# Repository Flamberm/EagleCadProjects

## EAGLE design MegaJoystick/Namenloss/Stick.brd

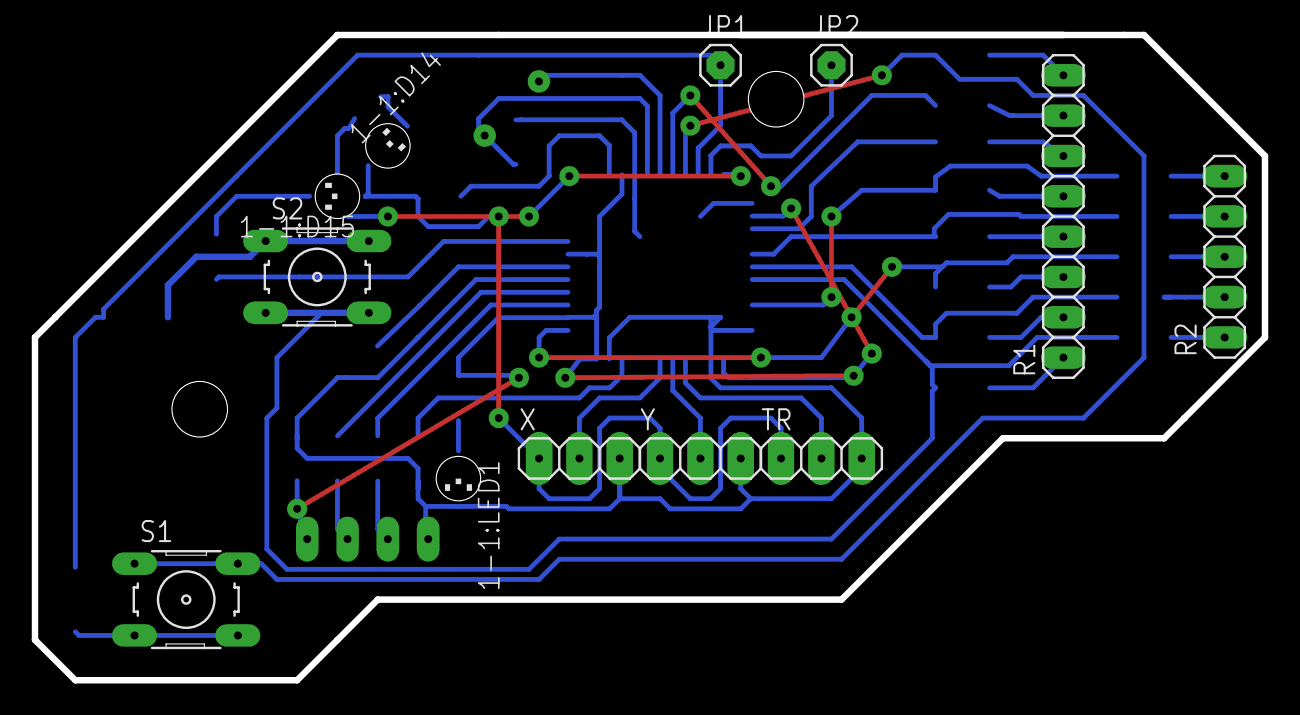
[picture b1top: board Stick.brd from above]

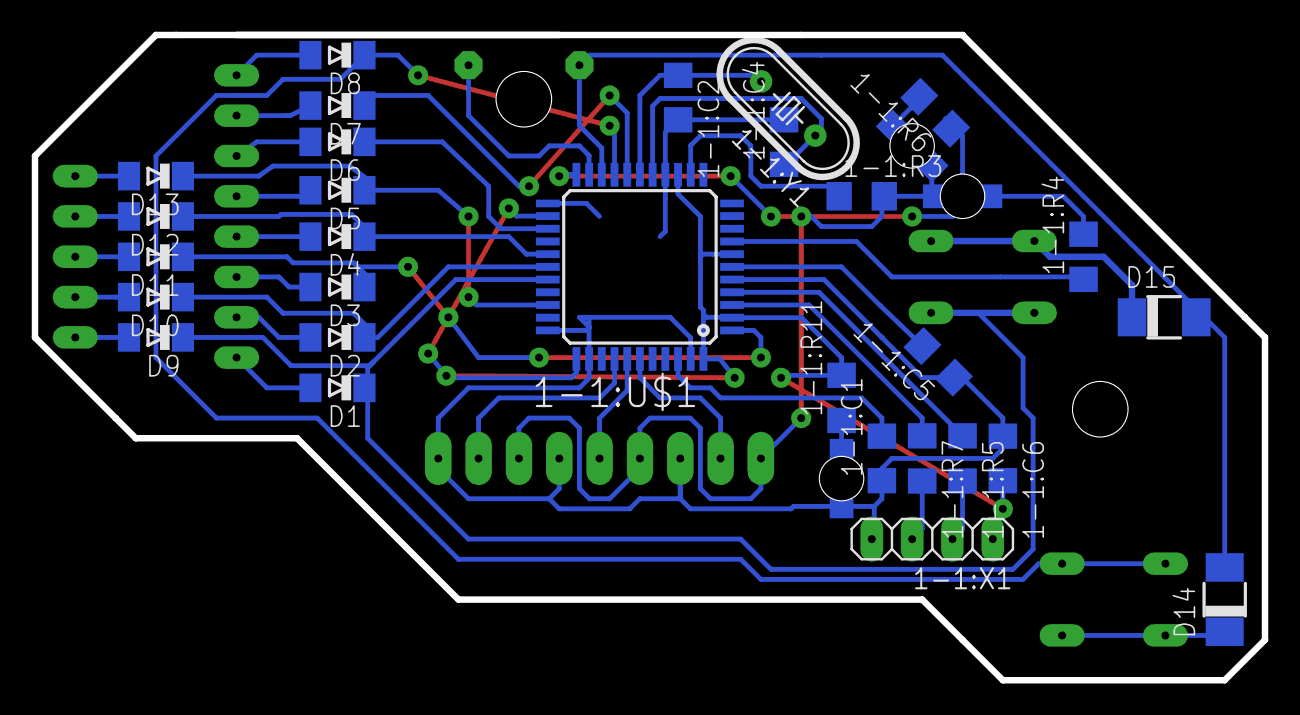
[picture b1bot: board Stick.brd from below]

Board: 2 copper layers, 77.5 x 40.6 mm, 42 parts (29 on the bottom side), 45 nets.

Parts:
1-1:C1, 1-1:C5, 1-1:C6: 10uF; C1206
1-1:C2, 1-1:C4: 22pF; C1206
1-1:D14: GREEN; LED1206
1-1:D15: RED; LED1206
1-1:FRAME1: FRAME-LETTER; CREATIVE_COMMONS
1-1:LED1: BLUE; LED1206
1-1:R3: 10K; R1206
1-1:R4: 300R; R1206
1-1:R5, 1-1:R7: 27R; R1206
1-1:R6, 1-1:R11: 390R; R1206
1-1:U$1: ATMEGA32U4-AU; TQFP44
1-1:X1: 1X04
1-1:Y1: 16MHz; HC49/S
D1, D2, D3, D4, D5, D6, D7, D8, D9, D10, D11, D12, D13: MINIMELF
D14, D15: DO-214AC
JP1, JP2: 1X01
R1: 1X08
R2: 1X05
S1, S2: B3F-10XX
TR: 1X03
X: 1X03
Y: 1X03

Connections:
1-1:3.3V: 1-1:C6.2, 1-1:R11.2, 1-1:U$1.2, 1-1:U$1.7, 1-1:U$1.14, 1-1:U$1.24, 1-1:U$1.34, 1-1:U$1.44, 1-1:X1.1
1-1:AREF: 1-1:C1.2, 1-1:U$1.42
1-1:D14: 1-1:R4.1, 1-1:U$1.8
1-1:D+: 1-1:R5.1, 1-1:U$1.4
1-1:D-: 1-1:R7.1, 1-1:U$1.3
1-1:N$23: 1-1:C4.1, 1-1:U$1.16, 1-1:Y1.1
1-1:N$24: 1-1:C2.1, 1-1:U$1.17, 1-1:Y1.2
1-1:N$25: 1-1:C5.2, 1-1:U$1.6
1-1:N$26: 1-1:R7.2, 1-1:X1.3
1-1:N$27: 1-1:R5.2, 1-1:X1.2
1-1:N$29: 1-1:D15.C, 1-1:R4.2
1-1:N$30: 1-1:D14.C, 1-1:R6.2
1-1:N$38: 1-1:LED1.A, 1-1:R11.1
1-1:RESET: 1-1:R3.1, 1-1:U$1.13
1-1:TXLED: 1-1:R6.1, 1-1:U$1.22
D2: 1-1:U$1.19, D8.C, S1.1, S1.2
D9: 1-1:U$1.29, D1.C, D9.C, S2.3, S2.4
GND: 1-1:C1.1, 1-1:C2.2, 1-1:C4.2, 1-1:C5.1, 1-1:C6.1, 1-1:LED1.C, 1-1:U$1.5, 1-1:U$1.15, 1-1:U$1.23, 1-1:U$1.33, 1-1:U$1.35, 1-1:U$1.43, 1-1:X1.4, TR.3, X.3, Y.3
unnamed: D15.C, S2.1, S2.2
unnamed: 1-1:U$1.21, JP2.1
unnamed: D1.A, R1.1
unnamed: D2.A, R1.2
unnamed: D3.A, R1.3
unnamed: D4.A, R1.4
unnamed: D5.A, R1.5
unnamed: D6.A, R1.6
unnamed: D7.A, R1.7
unnamed: D8.A, R1.8
unnamed: D9.A, R2.1
unnamed: D10.A, R2.2
unnamed: D11.A, R2.3
unnamed: D12.A, R2.4
unnamed: D13.A, R2.5
unnamed: 1-1:D14.A, 1-1:D15.A, 1-1:R3.2, TR.1, X.1, Y.1
unnamed: 1-1:U$1.39, X.2
unnamed: 1-1:U$1.38, Y.2
unnamed: 1-1:U$1.37, TR.2
unnamed: D14.C, S1.3, S1.4
R2: 1-1:U$1.28, D2.C, D10.C
R3: 1-1:U$1.1, D3.C, D11.C
R4: 1-1:U$1.27, D4.C, D12.C
R5: 1-1:U$1.31, D5.C, D13.C
R6: 1-1:U$1.25, D6.C
R7: 1-1:U$1.18, D7.C
RXI: 1-1:U$1.20, D14.A, D15.A, JP1.1

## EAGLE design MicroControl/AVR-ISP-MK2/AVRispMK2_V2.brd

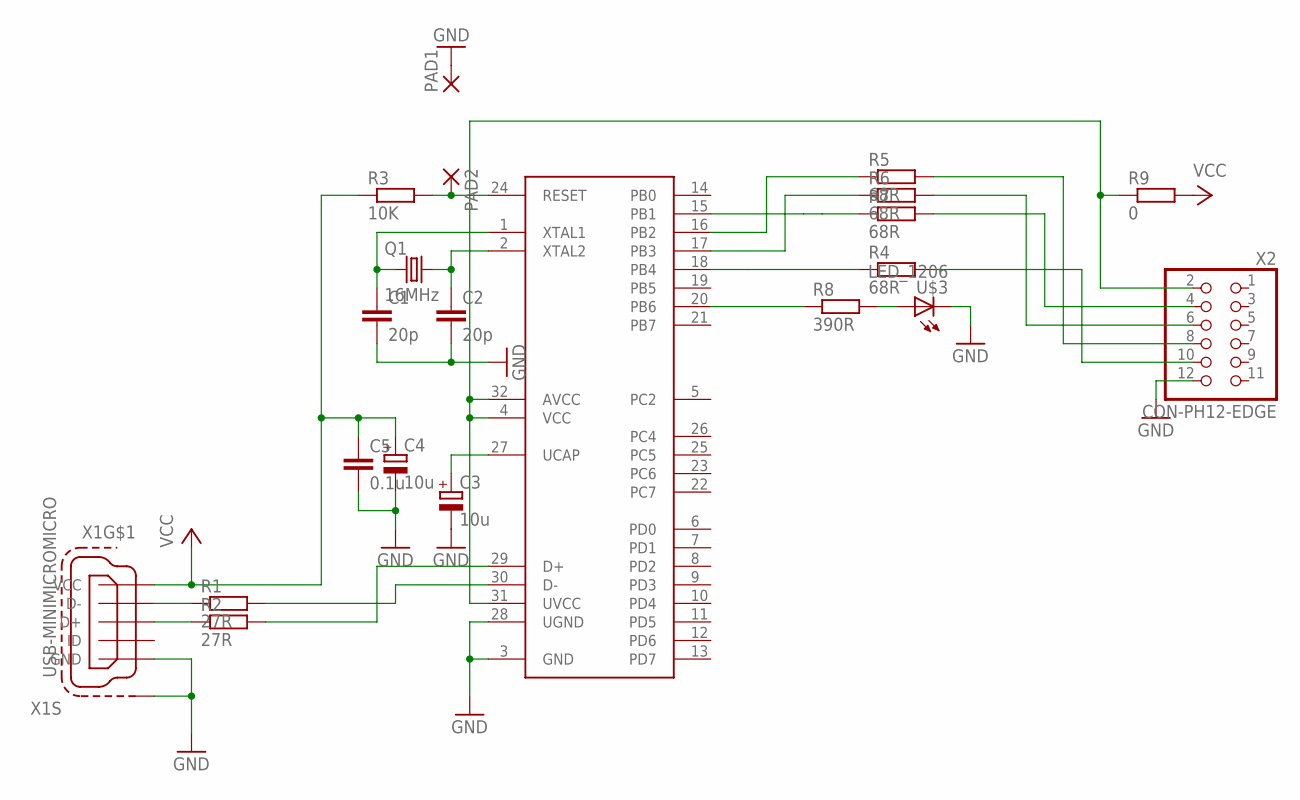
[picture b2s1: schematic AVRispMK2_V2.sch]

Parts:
C1, C2: 20p; C1206
C3, C4: 10u; SMC_A
C5: 0.1u; C1206
PAD1, PAD2: SMD2; SMD1,27-2,54
Q1: 16MHz; CRYSTAL-3225
R1, R2: 27R; R1206
R3: 10K; R1206
R4, R5, R6, R7: 68R; R1206
R8: 390R; R1206
R9: 0; R1206
U$1: AT90USB162; VQFP32
U$3: LED_1206; LED1206
X1: USB-MINIMICROMICRO; USB-B-MICRO-SMD
X2: CON-PH12-EDGE; ML12_EDGE_SMD

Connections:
!RST: R4.2, X2.10
GND: C1.2, C2.2, C3.-, C4.-, C5.2, PAD1.1, U$1.3 (GND), U$1.28 (UGND), U$3.C, X1.GND, X1.SHIELD1 (S1), X1.SHIELD2 (S1), X1.SHIELD3 (S1), X2.12
MISO: R6.2, X2.6
MOSI: R5.2, X2.8
unnamed: R2.1, X1.D+
unnamed: R1.1, X1.D-
unnamed: C1.1, Q1.P$2 (1), U$1.1 (XTAL1)
unnamed: C2.1, Q1.P$4 (2), U$1.2 (XTAL2)
unnamed: R1.2, U$1.30 (D-)
unnamed: R2.2, U$1.29 (D+)
unnamed: C3.+, U$1.27 (UCAP)
unnamed: PAD2.1, R3.2, U$1.24 (RESET)
unnamed: R8.1, U$1.20 (PB6)
unnamed: R8.2, U$3.A
unnamed: R4.1, U$1.18 (PB4)
unnamed: R6.1, U$1.17 (PB3)
unnamed: R5.1, U$1.16 (PB2)
unnamed: R7.1, U$1.15 (PB1)
SCK: R7.2, X2.4
VCC: C4.+, C5.1, R3.1, R9.2, X1.VBUS (VCC)
VTRG: R9.1, U$1.4 (VCC), U$1.31 (UVCC), U$1.32 (AVCC), X2.2

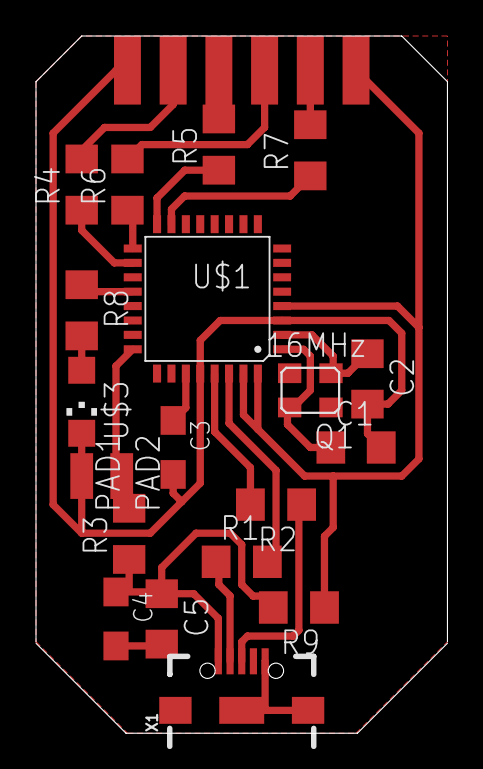
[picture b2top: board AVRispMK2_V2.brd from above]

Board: 2 copper layers, 22.9 x 38.7 mm, 21 parts (1 on the bottom side), 21 nets.

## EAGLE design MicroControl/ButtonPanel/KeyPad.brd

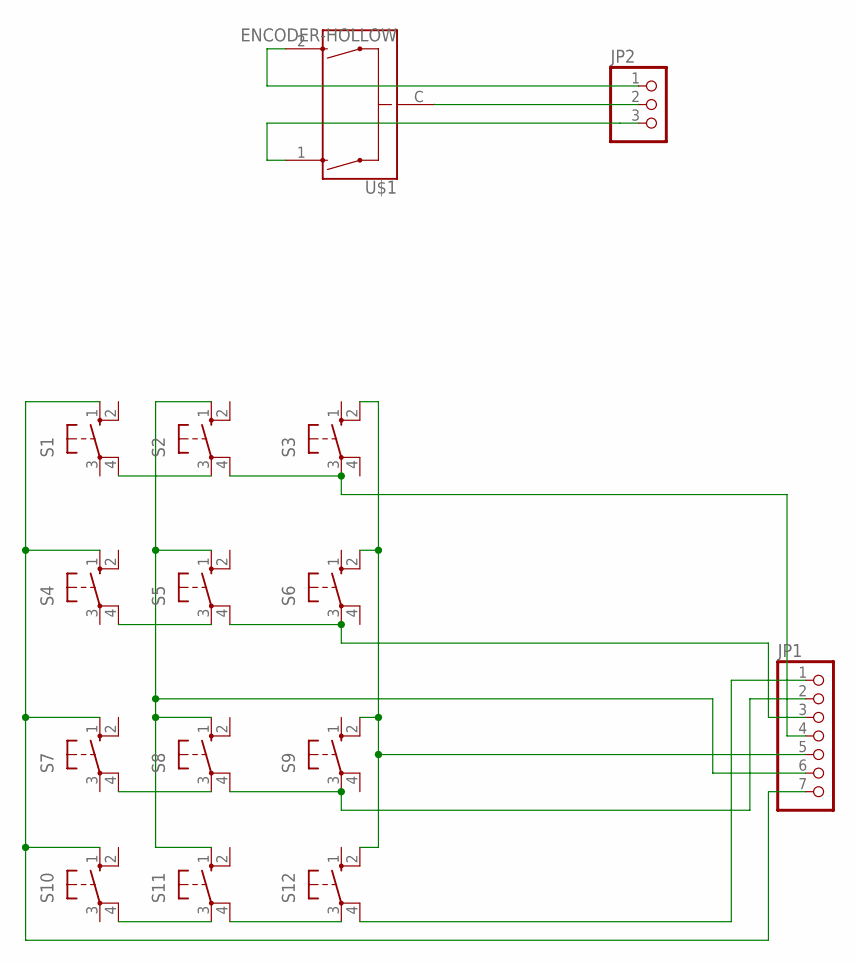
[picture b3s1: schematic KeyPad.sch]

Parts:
JP1: PINHD-1X7/90; 1X07/90
JP2: PINHD-1X3/90; 1X03/90
S1, S2, S3, S4, S5, S6, S7, S8, S9, S10, S11, S12: 40-XX; B3F-40XX
U$1: ENCODER-HOLLOW; HOLLOW-ENCODER

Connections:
unnamed: JP2.2, U$1.C
unnamed: JP2.1, U$1.2 (B)
unnamed: JP2.3, U$1.1 (A)
unnamed: S10.4 (P1), S11.3
unnamed: S11.4 (P1), S12.3
unnamed: JP1.2, S8.4 (P1), S9.3
unnamed: S7.4 (P1), S8.3
unnamed: S4.4 (P1), S5.3
unnamed: JP1.3, S5.4 (P1), S6.3
unnamed: S1.4 (P1), S2.3
unnamed: JP1.4, S2.4 (P1), S3.3
unnamed: JP1.1, S12.4 (P1)
unnamed: JP1.7, S1.1 (S), S4.1 (S), S7.1 (S), S10.1 (S)
unnamed: JP1.6, S2.1 (S), S5.1 (S), S8.1 (S), S11.1 (S)
unnamed: JP1.5, S3.2 (S1), S6.2 (S1), S9.2 (S1), S12.2 (S1)

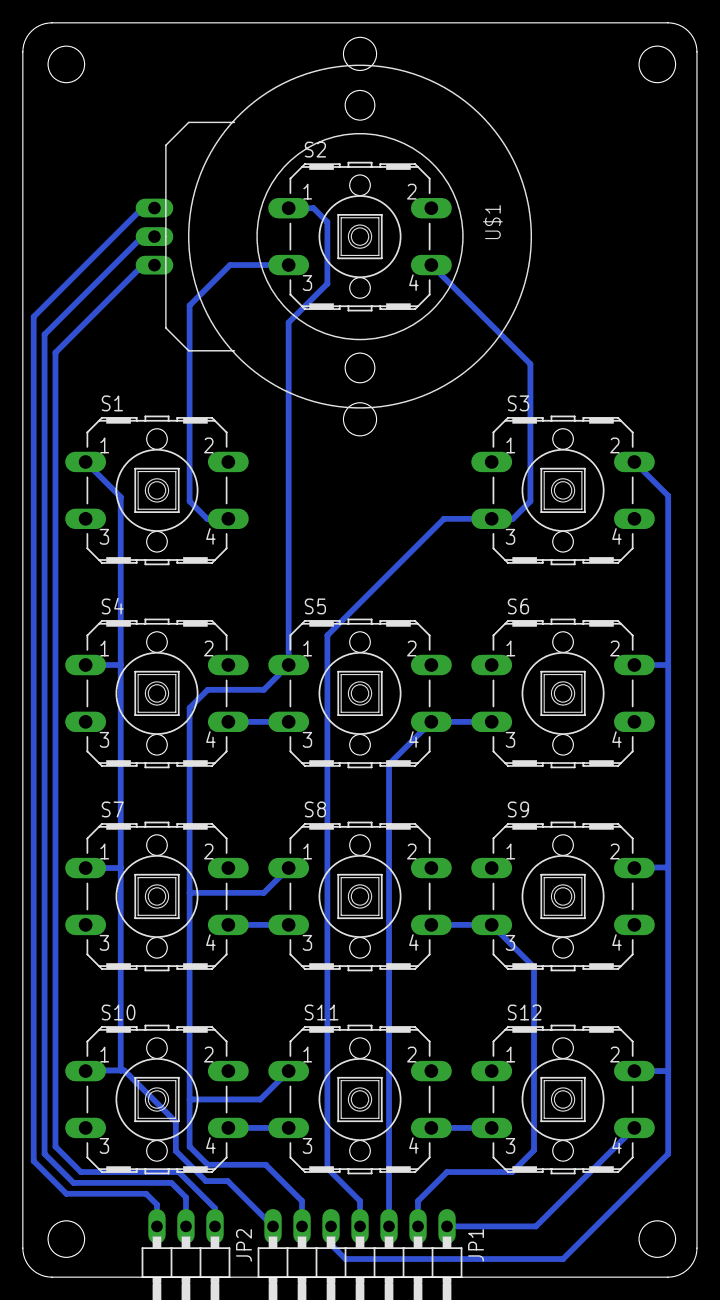
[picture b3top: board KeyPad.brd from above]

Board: 2 copper layers, 59.0 x 109.8 mm, 15 parts (0 on the bottom side), 15 nets.

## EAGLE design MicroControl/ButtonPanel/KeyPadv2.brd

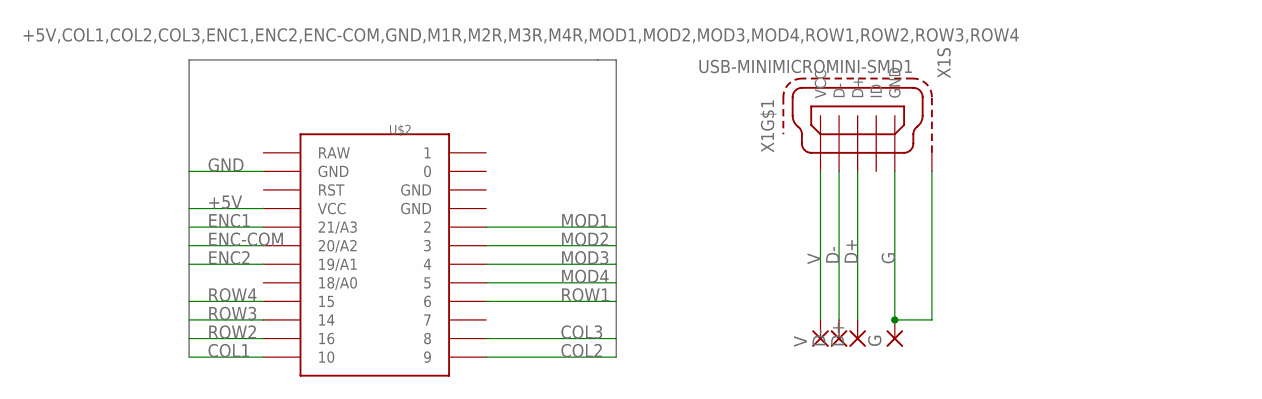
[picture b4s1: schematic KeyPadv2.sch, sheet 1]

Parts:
D+: SMD2; SMD1,27-2,54
D-: SMD2; SMD1,27-2,54
G: SMD2; SMD1,27-2,54
U$2: PROMICRO
V: SMD2; SMD1,27-2,54
X1: USB-MINIMICROMINI-SMD1; 32005-201

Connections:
0: U$2.0
1: U$2.1
+5V: U$2.VCC
COL1: U$2.10; also elsewhere on the board
COL2: U$2.9; also elsewhere on the board
COL3: U$2.8; also elsewhere on the board
D+: D+.1, X1.3 (D+)
D-: D-.1, X1.2 (D-)
ENC1: U$2.21/A3; also elsewhere on the board
ENC2: U$2.19/A1; also elsewhere on the board
ENC-COM: U$2.20/A2; also elsewhere on the board
G: G.1, X1.5 (GND), X1.M1 (S1), X1.M2 (S1), X1.M3 (S1), X1.M4 (S1)
GND: U$2.GND@1 (GND), U$2.GND@2 (GND); also elsewhere on the board
MOD1: U$2.2; also elsewhere on the board
MOD2: U$2.3; also elsewhere on the board
MOD3: U$2.4; also elsewhere on the board
MOD4: U$2.5; also elsewhere on the board
RAW: U$2.RAW
ROW1: U$2.6; also elsewhere on the board
ROW2: U$2.16; also elsewhere on the board
ROW3: U$2.14; also elsewhere on the board
ROW4: U$2.15; also elsewhere on the board
V: V.1, X1.1 (VCC)

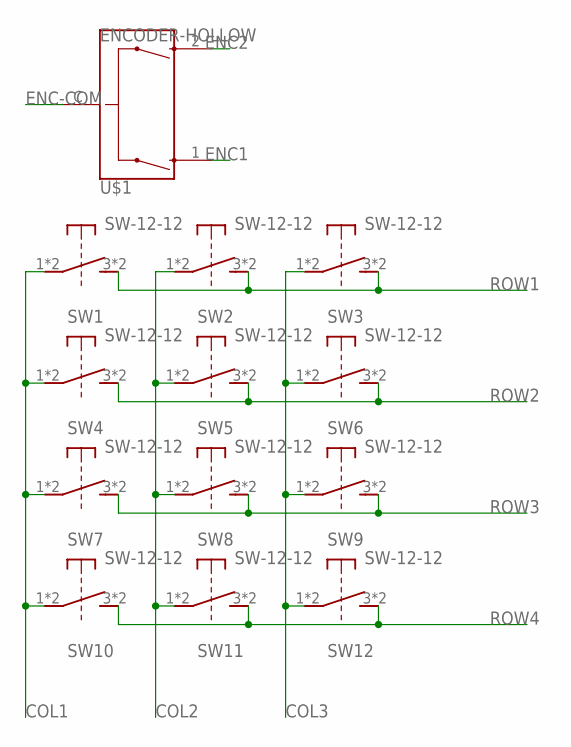
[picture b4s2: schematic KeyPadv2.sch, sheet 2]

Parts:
SW1, SW2, SW3, SW4, SW5, SW6, SW7, SW8, SW9, SW10, SW11, SW12: SW-12-12; B3F-40XX
U$1: ENCODER-HOLLOW; HOLLOW-ENCODER

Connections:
COL1: SW1.1, SW1.2 (1), SW4.1, SW4.2 (1), SW7.1, SW7.2 (1), SW10.1, SW10.2 (1); also elsewhere on the board
COL2: SW2.1, SW2.2 (1), SW5.1, SW5.2 (1), SW8.1, SW8.2 (1), SW11.1, SW11.2 (1); also elsewhere on the board
COL3: SW3.1, SW3.2 (1), SW6.1, SW6.2 (1), SW9.1, SW9.2 (1), SW12.1, SW12.2 (1); also elsewhere on the board
ENC1: U$1.1 (A); also elsewhere on the board
ENC2: U$1.2 (B); also elsewhere on the board
ENC-COM: U$1.C; also elsewhere on the board
ROW1: SW1.3 (2), SW1.4 (2), SW2.3 (2), SW2.4 (2), SW3.3 (2), SW3.4 (2); also elsewhere on the board
ROW2: SW4.3 (2), SW4.4 (2), SW5.3 (2), SW5.4 (2), SW6.3 (2), SW6.4 (2); also elsewhere on the board
ROW3: SW7.3 (2), SW7.4 (2), SW8.3 (2), SW8.4 (2), SW9.3 (2), SW9.4 (2); also elsewhere on the board
ROW4: SW10.3 (2), SW10.4 (2), SW11.3 (2), SW11.4 (2), SW12.3 (2), SW12.4 (2); also elsewhere on the board

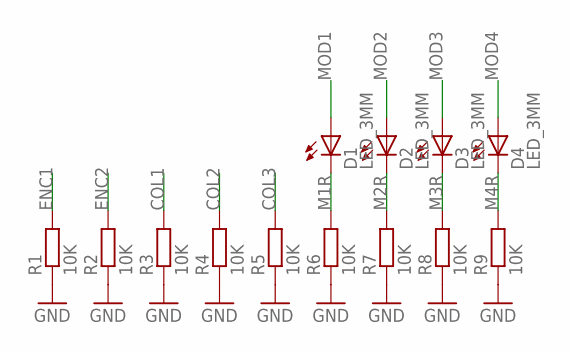
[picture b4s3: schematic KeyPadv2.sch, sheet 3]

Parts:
D1, D2, D3, D4: LED_3MM; LED3MM
R1, R2, R3, R4, R5, R6, R7, R8, R9: 10K; RESC3216X60

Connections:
COL1: R3.2; also elsewhere on the board
COL2: R4.2; also elsewhere on the board
COL3: R5.2; also elsewhere on the board
ENC1: R1.2; also elsewhere on the board
ENC2: R2.2; also elsewhere on the board
GND: R1.1, R2.1, R3.1, R4.1, R5.1, R6.1, R7.1, R8.1, R9.1; also elsewhere on the board
M1R: D1.K (C), R6.2
M2R: D2.K (C), R7.2
M3R: D3.K (C), R8.2
M4R: D4.K (C), R9.2
MOD1: D1.A; also elsewhere on the board
MOD2: D2.A; also elsewhere on the board
MOD3: D3.A; also elsewhere on the board
MOD4: D4.A; also elsewhere on the board

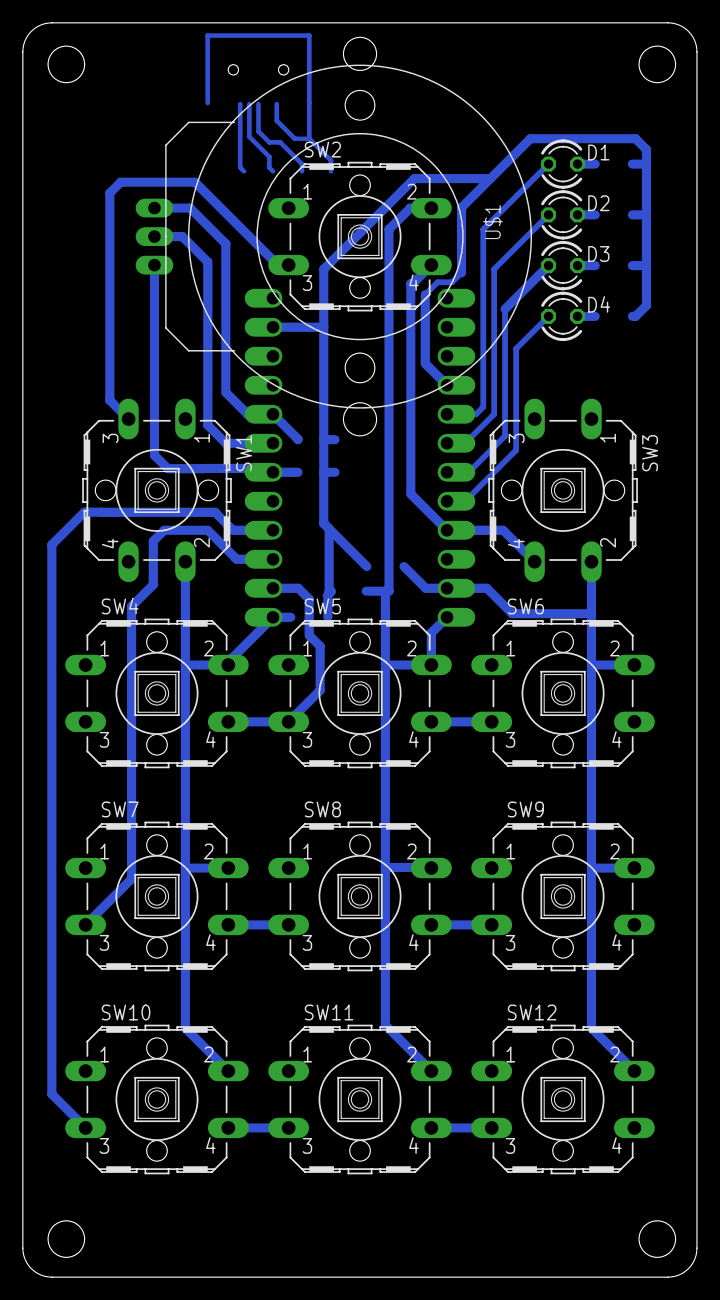
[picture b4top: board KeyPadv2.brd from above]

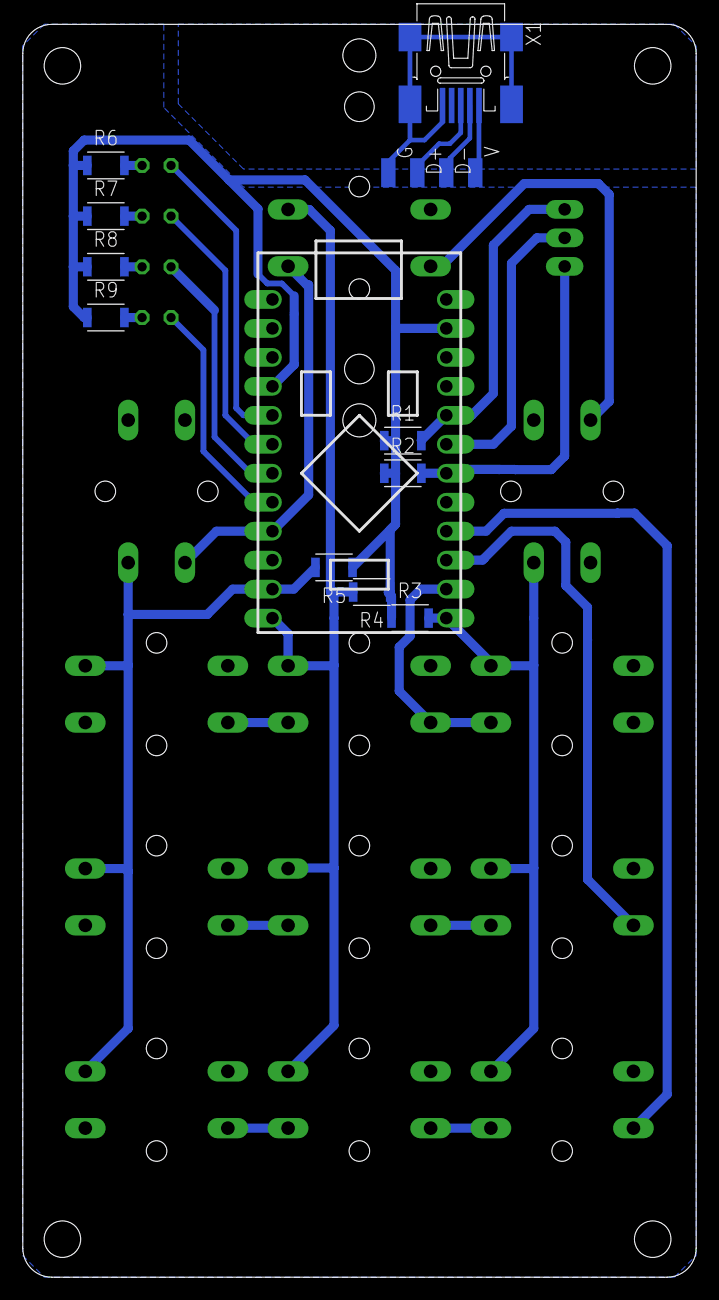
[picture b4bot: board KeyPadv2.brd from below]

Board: 2 copper layers, 59.0 x 109.8 mm, 32 parts (15 on the bottom side), 23 nets.

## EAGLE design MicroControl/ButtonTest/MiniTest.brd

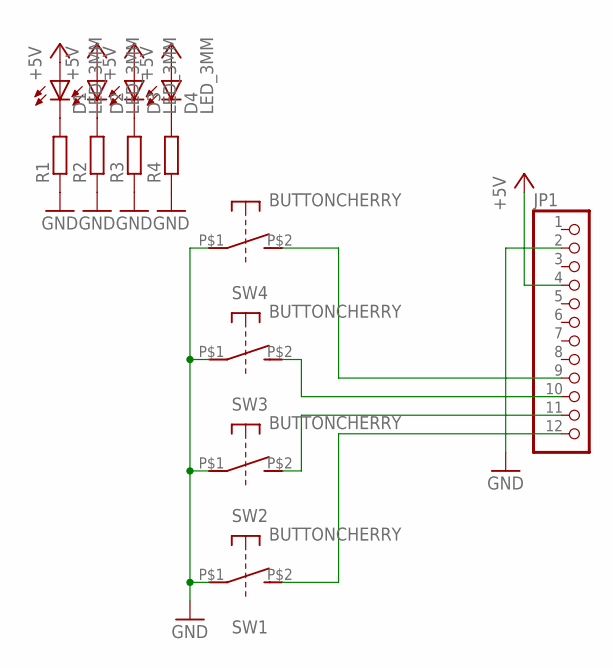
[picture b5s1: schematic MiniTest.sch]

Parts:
D1, D2, D3, D4: LED_3MM; LED3MM
JP1: PINHD-1X12; 1X12
R1, R2, R3, R4: R_R1206; RESC3216X60
SW1, SW2, SW3, SW4: BUTTONCHERRY; SW_GATERON

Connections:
+5V: D1.A, D2.A, D3.A, D4.A, JP1.4
GND: JP1.2, R1.1, R2.1, R3.1, R4.1, SW1.P$1 (1), SW2.P$1 (1), SW3.P$1 (1), SW4.P$1 (1)
unnamed: JP1.9, SW4.P$2 (2)
unnamed: JP1.10, SW3.P$2 (2)
unnamed: JP1.11, SW2.P$2 (2)
unnamed: JP1.12, SW1.P$2 (2)
unnamed: D1.K (C), R1.2
unnamed: D2.K (C), R2.2
unnamed: D3.K (C), R3.2
unnamed: D4.K (C), R4.2

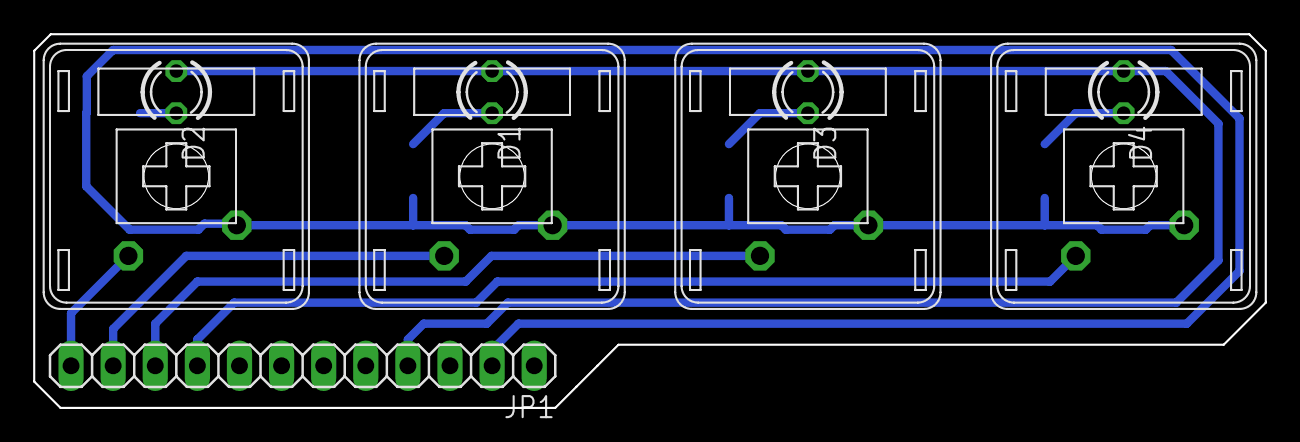
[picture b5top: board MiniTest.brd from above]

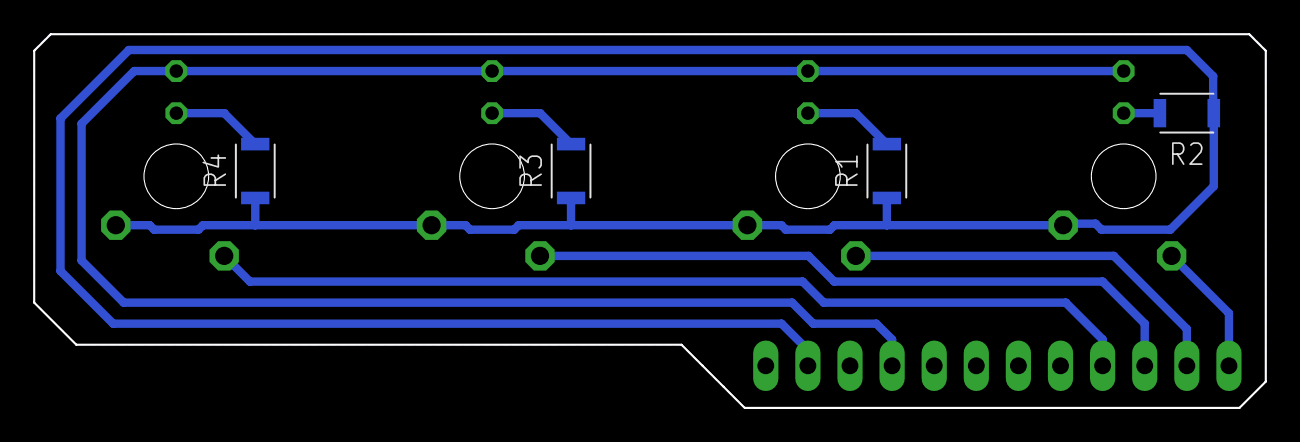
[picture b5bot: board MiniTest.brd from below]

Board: 2 copper layers, 74.3 x 22.5 mm, 13 parts (4 on the bottom side), 10 nets.

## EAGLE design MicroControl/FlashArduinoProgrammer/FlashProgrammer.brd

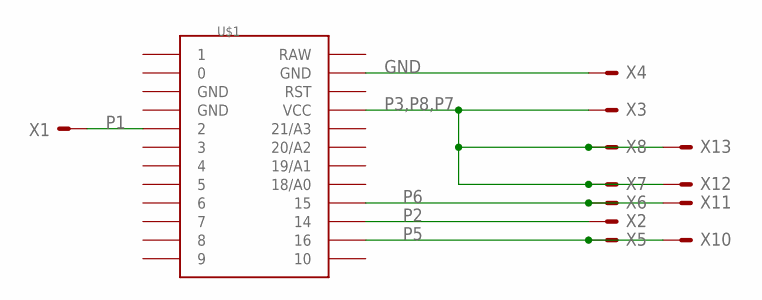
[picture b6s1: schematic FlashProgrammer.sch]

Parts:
U$1: PROMICRO
X1, X2, X3, X4, X5, X6, X7, X8, X10, X11, X12, X13: POGOPIN

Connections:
0: U$1.0
1: U$1.1
GND: U$1.GND@1 (GND), U$1.GND@2 (GND), X4.P$1
P1: U$1.2, X1.P$1
P2: U$1.14, X2.P$1
P3,P8,P7: U$1.VCC, X3.P$1, X7.P$1, X8.P$1, X12.P$1, X13.P$1
P5: U$1.16, X5.P$1, X10.P$1
P6: U$1.15, X6.P$1, X11.P$1
RAW: U$1.RAW

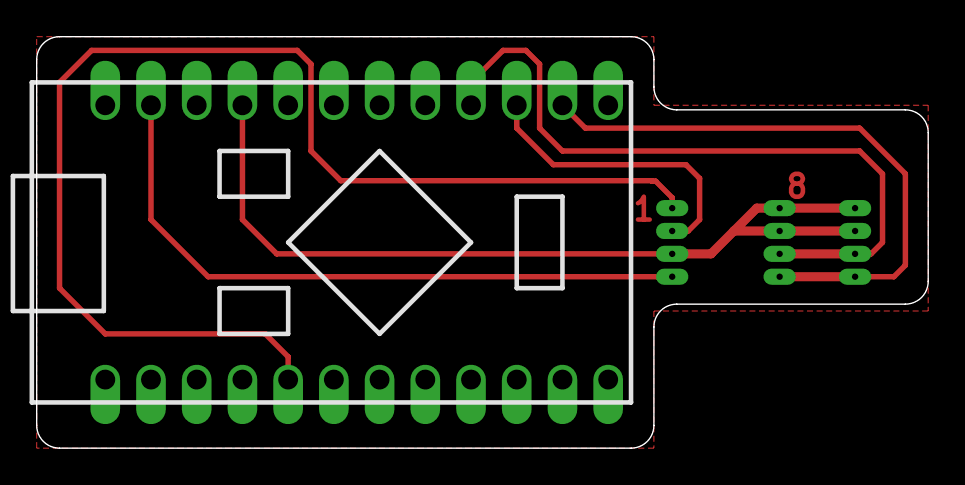
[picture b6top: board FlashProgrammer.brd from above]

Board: 2 copper layers, 49.5 x 22.9 mm, 13 parts (0 on the bottom side), 6 nets.

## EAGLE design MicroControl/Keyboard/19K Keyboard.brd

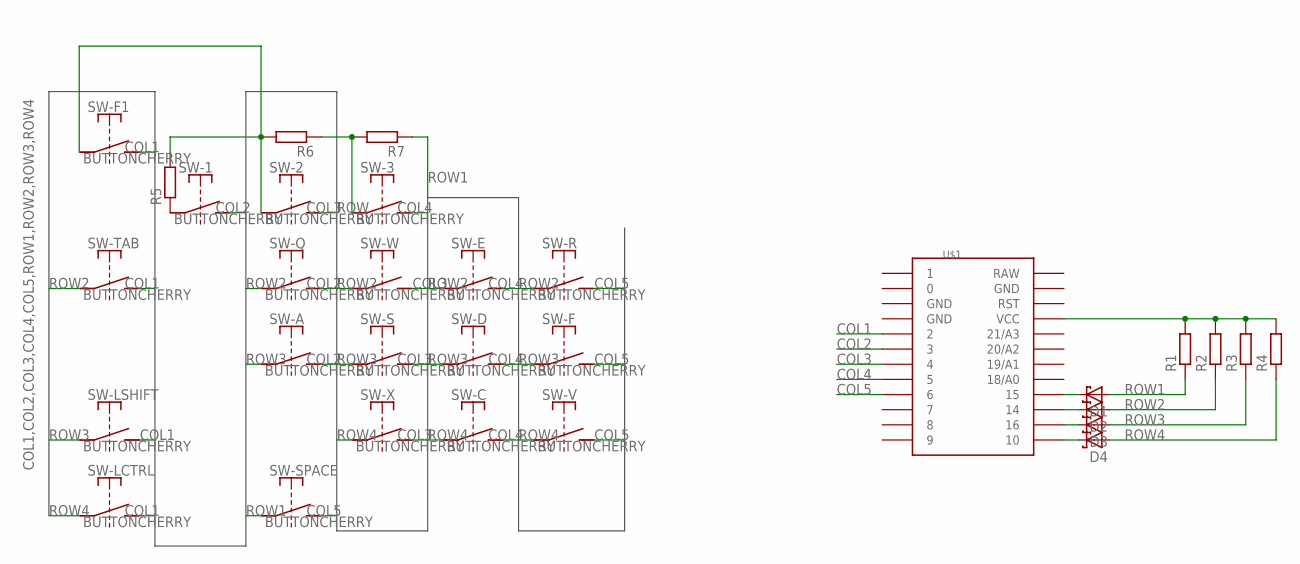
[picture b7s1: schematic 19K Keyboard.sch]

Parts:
D1, D2, D3, D4: DIODE-SH_SOD523; SODFL1608X65
R1, R2, R3, R4: R_R1206; RESC3216X60
R5, R6, R7: R_R0805; RESC2012X50
SW-1, SW-2, SW-3: BUTTONCHERRY; SW_GATERON
SW-A: BUTTONCHERRY; SW_GATERON
SW-C: BUTTONCHERRY; SW_GATERON
SW-D: BUTTONCHERRY; SW_GATERON
SW-E: BUTTONCHERRY; SW_GATERON
SW-F, SW-F1: BUTTONCHERRY; SW_GATERON
SW-LCTRL: BUTTONCHERRY; SW_GATERON
SW-LSHIFT: BUTTONCHERRY; SW_GATERON
SW-Q: BUTTONCHERRY; SW_GATERON
SW-R: BUTTONCHERRY; SW_GATERON
SW-S: BUTTONCHERRY; SW_GATERON
SW-SPACE: BUTTONCHERRY; SW_GATERON
SW-TAB: BUTTONCHERRY; SW_GATERON
SW-V: BUTTONCHERRY; SW_GATERON
SW-W: BUTTONCHERRY; SW_GATERON
SW-X: BUTTONCHERRY; SW_GATERON
U$1: PROMICRO

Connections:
0: U$1.0
1: U$1.1
COL1: SW-F1.P$2 (2), SW-LCTRL.P$2 (2), SW-LSHIFT.P$2 (2), SW-TAB.P$2 (2), U$1.2
COL2: SW-1.P$2 (2), SW-A.P$2 (2), SW-Q.P$2 (2), U$1.3
COL3: SW-2.P$2 (2), SW-S.P$2 (2), SW-W.P$2 (2), SW-X.P$2 (2), U$1.4
COL4: SW-3.P$2 (2), SW-C.P$2 (2), SW-D.P$2 (2), SW-E.P$2 (2), U$1.5
COL5: SW-F.P$2 (2), SW-R.P$2 (2), SW-SPACE.P$2 (2), SW-V.P$2 (2), U$1.6
GND: U$1.GND@1 (GND), U$1.GND@2 (GND)
unnamed: D1.1 (C), U$1.15
unnamed: D2.1 (C), U$1.14
unnamed: D3.1 (C), U$1.16
unnamed: D4.1 (C), U$1.10
unnamed: R5.1, SW-1.P$1 (1)
unnamed: R5.2, R6.2, SW-2.P$1 (1), SW-F1.P$1 (1)
unnamed: R1.2, R2.2, R3.2, R4.2, U$1.VCC
RAW: U$1.RAW
ROW: R6.1, R7.2, SW-3.P$1 (1)
ROW1: D1.2 (A), R1.1, R7.1, SW-SPACE.P$1 (1)
ROW2: D2.2 (A), R2.1, SW-E.P$1 (1), SW-Q.P$1 (1), SW-R.P$1 (1), SW-TAB.P$1 (1), SW-W.P$1 (1)
ROW3: D3.2 (A), R3.1, SW-A.P$1 (1), SW-D.P$1 (1), SW-F.P$1 (1), SW-LSHIFT.P$1 (1), SW-S.P$1 (1)
ROW4: D4.2 (A), R4.1, SW-C.P$1 (1), SW-LCTRL.P$1 (1), SW-V.P$1 (1), SW-X.P$1 (1)

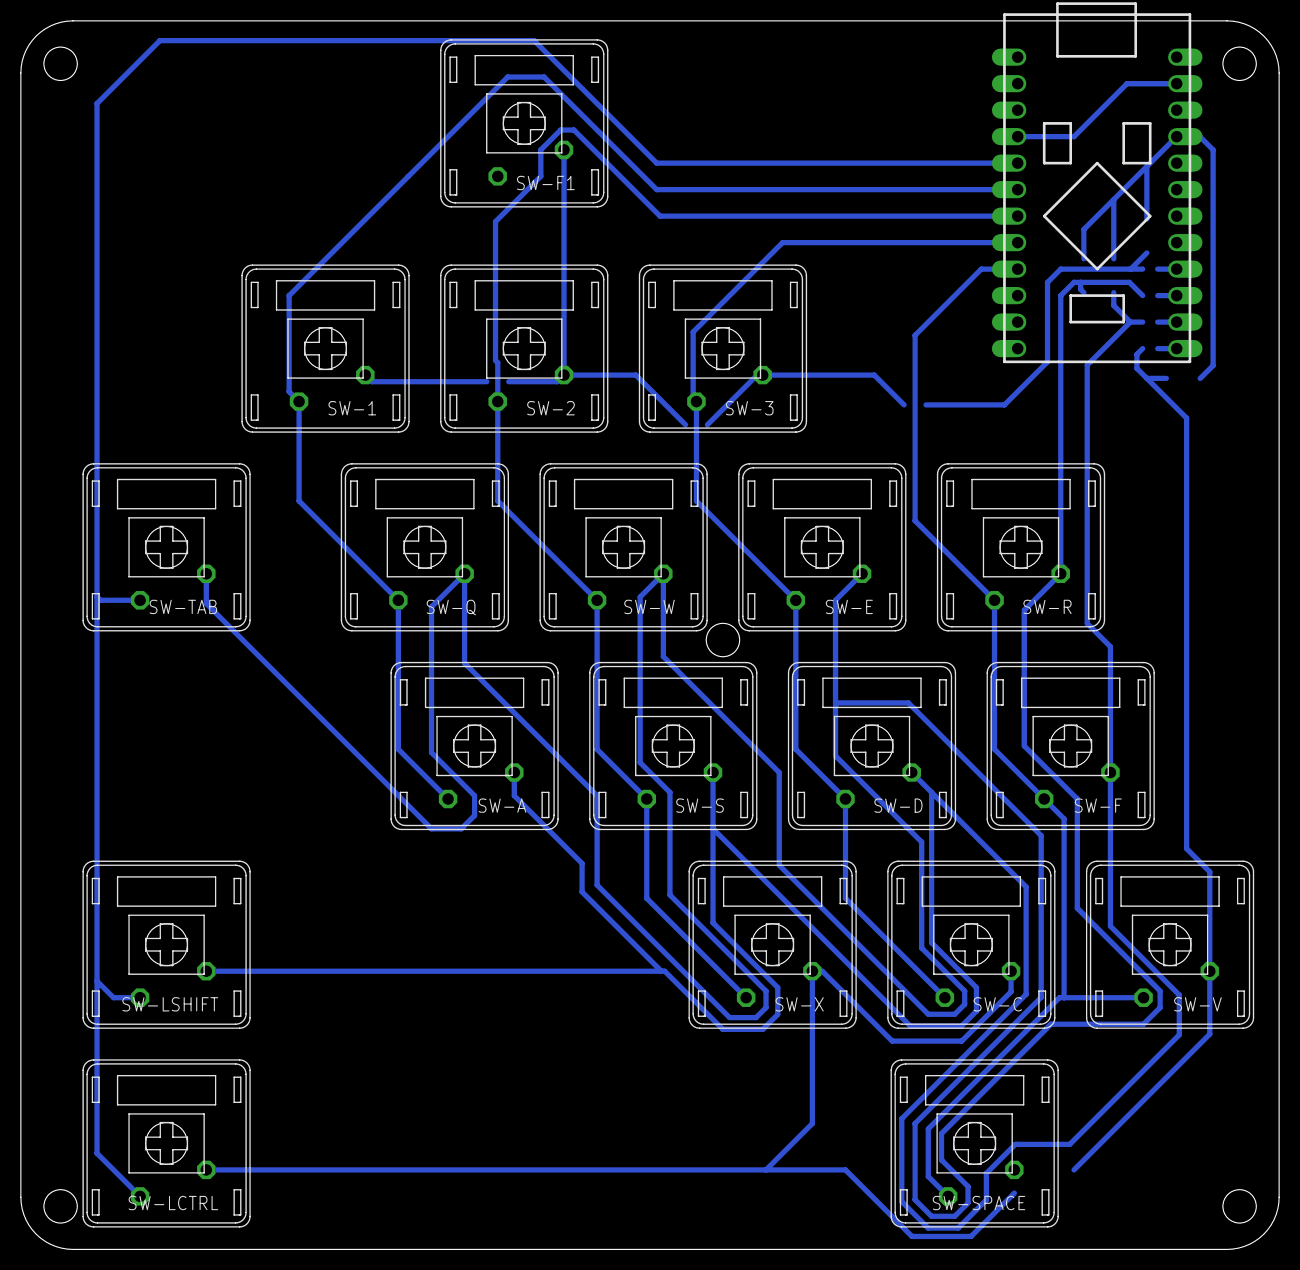
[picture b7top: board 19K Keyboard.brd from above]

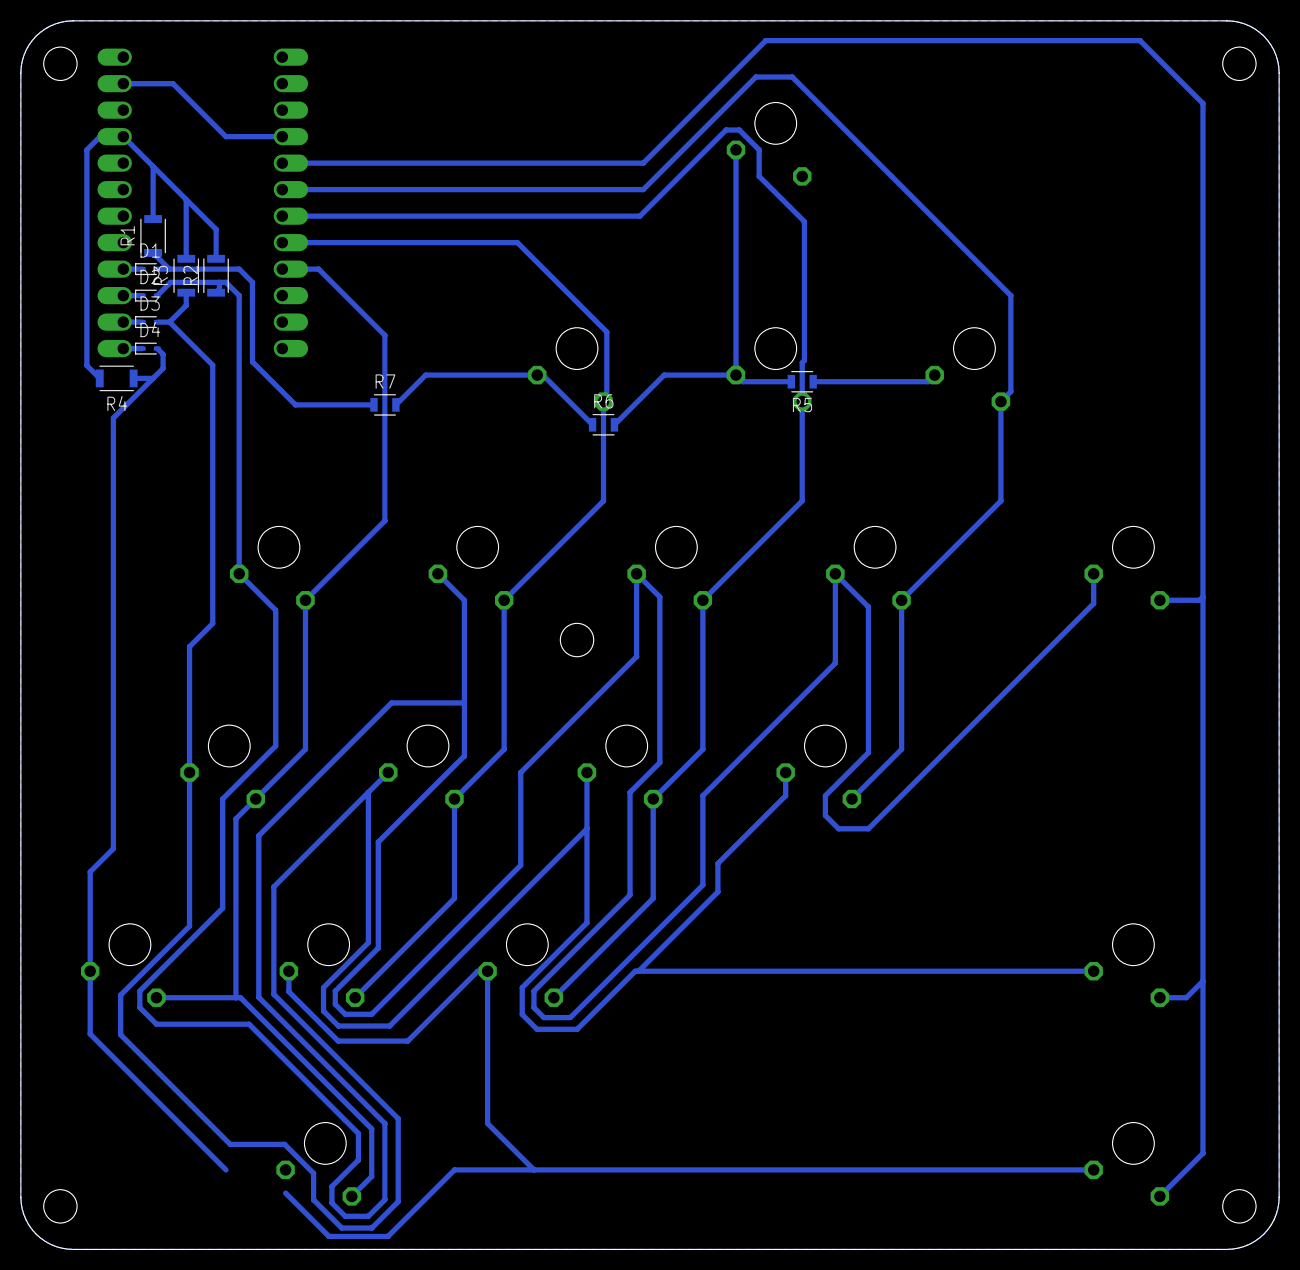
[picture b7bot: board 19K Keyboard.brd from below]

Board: 2 copper layers, 120.6 x 117.8 mm, 31 parts (11 on the bottom side), 18 nets.

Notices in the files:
parts and their libraries:
SparkFun-Aesthetics: Licensing: CC v3.0 Share-Alike You are welcome to use this library for commercial purposes.
SparkFun-Aesthetics: Released under the Creative Commons Attribution Share-Alike 3.0 License
SparkFun-Aesthetics: http://creativecommons.org/licenses/by-sa/3.0
